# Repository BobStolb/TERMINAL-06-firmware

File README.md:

# TERMINAL-06 firmware

Six-digit Soviet nixie tube clock firmware — 4x IN-12A (HH:MM) + 2x IN-17 (SS),
built on Arduino Nano / ATmega328P.

Derived from [AlexGyver's NixieClock v2.5](https://github.com/AlexGyver/NixieClock_v2)
(MIT-spirited open project). Keep the original attribution if you redistribute
this source — see the header of `nixieClock_TS06.ino`.

## What's in here

- `firmware/nixieClock_TS06/` — the main clock sketch. Open
  `nixieClock_TS06.ino` in the Arduino IDE; the other `.ino` files in the same
  folder are tabs of the same sketch and compile together automatically.
  `nixieClock_TS06.hex` alongside them is a precompiled build — flashable
  directly with avrdude if you don't want to rebuild from source.
- `firmware/secCathodeMap/` — a standalone bench jig (its own `setup()`/
  `loop()`, deliberately kept in a separate sketch folder from the main
  firmware so the two don't collide at compile time). Run it once per new
  SEC module to map IN-17 cathodes to K155ID1 pins — see the comment header
  in `secCathodeMap.ino` for the full procedure.
- `libraries/` — actual source for the third-party libraries this sketch
  depends on: `GyverButton/` and `RTClib/`, each in the standard Arduino
  library layout (`.h`/`.cpp`, `library.properties`, examples). To build
  from scratch, copy both folders into your Arduino sketchbook's
  `libraries/` directory before compiling. Wire and EEPROM are built into
  the Arduino AVR core and don't need anything extra.

## Status vs. the project spec (as of 28.08.26)

This code is the display-layer port described in `TERMINAL-06-spec.md` §5:
six-tube multiplex ISR (Timer2 at AlexGyver's original prescaler 8, 50 Hz
refresh with 640 us of optocoupler dead time — see MULTIPLEX TIMING in the
sketch), anti-poisoning and glitch effects extended to all six tubes (both
now switchable off at build time, and currently off pending bench sign-off
of the timing), buzzer removed (D2 reused),
old rev B control scheme (2 buttons + 1 lever) — not the rotary/lever panel
described elsewhere in the project, which is a later firmware milestone.

**One known discrepancy, not yet fixed here:** the spec states `DOT_BRIGHT`
was retuned for neon (170/90) instead of the LED-era default (35/15), but
this source still has `DOT_BRIGHT 35` / `DOT_BRIGHT_N 15`
(`nixieClock_TS06.ino`). Doesn't affect the digit-multiplex testing this
firmware is used for (P2 in the prototype plan), but worth fixing before the
colon step (P6).

## Board settings for flashing

Arduino IDE: Board = Arduino Nano, Processor = ATmega328P. If upload fails
with a programmer-not-responding error, switch Processor to
"ATmega328P (Old Bootloader)" — common on CH340-based Nano clones.

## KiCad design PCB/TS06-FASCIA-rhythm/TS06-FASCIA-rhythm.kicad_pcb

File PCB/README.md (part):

# TERMINAL-06 — custom PCBs

The fascia goes to Rezonit with the clock's electronics. For a small production run, the electronics are the through-hole pair **TS06-DISP + TS06-DRV**: tubes on one board, everything else on the one behind it, no vias on either. The one-board TS06-MAIN is kept, with its history. A tube board of the old kind is deliberately deferred.

| Board | Size | Stack | Status |
|---|---|---|---|
| **TS06-FASCIA** | 176 × 40 mm | 2.0 mm FR4, black mask, white silk, ENIG | Routed. The control panel AND the printed product face. One board, not two. Surface-mount build: no solder visible from the front. Height compressed from the original 52mm 2026-09 - see below. |
| **TS06-FASCIA-rhythm** (fascia R) | 191.4 × 40 mm | 2.0 mm FR4, black mask, white silk, ENIG | **The fascia of the order** (`fab/ORDER.md`). Controls on the tubes' grid, surface-mount on the back, no plated hole. **Rev B (7.10.26): J1 is an upright JST B6B-PH-SM4-TB** (top entry: the plug stands off the back and the wires leave straight back; rev A had the side-entry S6B-PH-SM4-TB, whose lead bent 90 + 12 degrees onto the floor and cost the case 7.3 mm) - `PCB/TS06-FASCIA-rhythm/J1-UPRIGHT.md`, `PCB/TS06-FASCIA-rhythm/bom.md`. The 176 TS06-FASCIA above is unchanged (it keeps the side-entry part). |
| **TS06-FASCIA-THT** | 176 × 52 mm | same stack, ENIG | Second build of the same board, routed. Through-hole, with the A6 divider ON the face. Pick one to fabricate; they are alternatives, not a pair. Not yet height-compressed (the SMD build was chosen for fabrication). |
| **TS06-DISP** + **TS06-DRV** | 191.4 × 44 mm + 191.4 × 100 mm | 1.6 mm, matte black | **The through-hole pair (25.09.26), the build for a small production run.** A display board with the tubes and nothing else, plugged by pin strips into a driver board behind it, the way AlexGyver builds his. **Zero vias on either board.** Both at rev B (30.09.26): TS06-DRV rev B is routed and merged, `tools/verify_pair.sh` gives 27 PASS, 0 FAIL, 0 SKIP, and the fab packages are in `../fab/`. Not ordered. See below. |
| **TS06-MAIN** / **TS06-MAIN-THT** | 176 × 96 mm | 1.6 mm, matte black | **The whole clock on one board**, two builds, one outline, one netlist. Placed and checked; routing in progress — see below. Replaces the inherited AlexGyver board, SEC and COLON. |
| ~~TS06-SEC~~ | 67 × 55 mm | 1.6 mm, matte black | **Superseded 17.09.26 by TS06-MAIN.** Surface-mount build routed and clean (1159 tracks, 79 vias); kept as the worked example of a hard placement and of the router. |
| ~~TS06-COLON~~ | 6.5 mm strip | — | **Superseded 17.09.26 by TS06-MAIN**, which carries the two ИНС-1 at the same measured positions. Placement only. |
| ~~TS06-TUBE~~ | — | — | **Deferred 08.09.26.** See below. |

## The two builds of the fascia

Same outline, same artwork, same netlist, same connector. They differ in one decision:
where the solder is.

* **TS06-FASCIA** — every pad is surface-mount on the back face. The customer sees black
  mask, white silkscreen and the decorative gold, and no joint anywhere. Routed with 64
  signal tracks, all on B.Cu, and **zero vias anywhere on the board** — F.Cu carries only
  the decorative gold, so no signal net can ever collide with it. GND is a pour over the
  back face, same as THT, and reaches all 7 GND pads on its own: R6 (the A7 pull-up) used
  to sit directly in the corridor the other five nets needed to reach J1, walling three
  GND pads (SW4.1, R8.2, R7.2) off from the plane with no B.Cu path a router could find at
  any trace width. Moving R6 out of that corridor — no other placement changed — opened it
  up enough that the pour alone closes the gap, confirmed by checking every GND pad against
  KiCad's own computed `filled_polygon`, not just this repo's simulated one. No stitch
  traces, no vias, nothing extra: placement fixed what routing couldn't.
* **TS06-FASCIA-THT** — the A6 resistor ladder is on the FRONT: five axial resistors above
  the rotary's seven landing holes, and the copper between them is bare, so the divider
  reads as a circuit rather than as decoration. Every other part is behind the panel with
  its front mask closed, so those holes show no gold ring. Routed with 34 tracks and no
  vias: the ladder on F.Cu under opened mask, six signals on B.Cu under mask, and GND as a
  pour over the whole back face.

`preview.svg` (`preview.png` too, where regenerated) in each board's folder is generated
by `tools/render.py` from the board file itself — front face and back face — so the board
can be looked at without opening KiCad.

**TS06-FASCIA height compression (2026-09).** The board felt oversized next to the tube
row, so it was cut from 52mm to 40mm tall. This was a pure translation, not a re-route:
every footprint, all 64 tracks, the GND pour and the silkscreen legend were shifted up by
a fixed 12mm (the dead margin above the control row - SR25's 12.5mm lever-throw keepout
was the real floor, not the visible knob bezel), then the board outline itself was
redrawn 12mm shorter. Nothing about the routing was redesigned, so R6's placement (still
load-bearing for the GND pour closing without vias, see above) is untouched. The two
mounting holes nearest the top edge are the one exception: they're anchored to the board
edge, not the control row, so they were NOT shifted, keeping their original 4.5mm inset
from the (new) top edge. All five checker tools pass clean and match the pre-compression
board's output exactly (same 2 pour islands, same 86% coverage, same 12-net agreement
with the schematic). One thing the pure translation did NOT fix on its own: the MODE
dial's decorative arc (position labels 1-6, their tick marks, and the "MODE" title)
was drawn for the old 26mm-radius-from-center clearance and clipped the new 14mm
budget - the checker tools don't validate silkscreen against the board edge, only
copper, so this needed its own pass. Fixed by rescaling the whole arc/tick/number
system by 0.789 (position 1, the tallest point, now sits at 12.5mm above center
instead of 15.84mm) and moving the "MODE" title from directly above the shaft to
its left, clear of position 1's tick - it was the single tallest element (19mm)
and didn't belong to the numbered fan, so it got its own placement rather than
being scaled with the rest. `checkpcb.py`'s rotary-keepout check had the rotary's position
hardcoded as a literal (30.0, 26.0) from the old layout - fixed to read the rotary
footprint's real position instead, since a checker that only works for one specific
layout isn't a checker. TS06-FASCIA-THT was not touched - the SMD build was the one
chosen for fabrication.

**Two leftovers of that compression, fixed 30.09.26.**
* **Five circles moved by half.** The compression moved each circle's end point up 12 mm
  but not its centre. The rotary's 25 mm body ring, on F.SilkS, would have printed as a
  34.7 mm ring 12 mm below the knob and run 3.3 mm off the bottom edge. Its four siblings
  (lever and button keepouts on User.1) had the same fault. These were the board's only 2
  KiCad DRC warnings. All five centres are moved up 12 mm, so each radius is horizontal
  again (12.5 and 12.0 mm). The body ring is back on User.1, where `tools/mkpcb.py` drew it.
* **A stale ground fill.** The stored GND fill reached 11.5 mm above the top edge, and
  Gerbers plot the stored fill. KiCad 10 refilled the pour and saved the board.

After both fixes:
* KiCad DRC: 0 violations and 0 unconnected, at every severity.
* `checkpcb`, `checkcopper` and `audit`: clean.
* `checkmatch`: agrees with the schematic.

**One picture outlived the fix.** `PCB/TS06-FASCIA-rhythm/composite-0-centred.png`, the
reference that the fascia variants are judged against, was drawn from a board older than
the ring fix. So it still showed the ring 12 mm below the knob, and the owner's review
reported it as "the SW1 white circle isn't centred on its hole". It is redrawn from the
fixed board. `tools/mkpcb_fascia_rhythm.py` now refuses to draw a composite from a board
whose F.SilkS ring encloses a control hole off-centre (`silk_rings_off_centre()`).
`tools/render_kicad.py` renders a board in KiCad 10 with the black mask and white silk
that are ordered.

**Fascia R, rev B (7.10.26): J1 is upright.** The footprint `TS06_JST_PH_B6B-PH-SM4-TB_Back` (KiCad's land pattern, mirrored in X for the back; SMD, no plated hole) keeps the pin order and the place between the buttons; the case model's floor rose from Y -7.3 to -4.5 (204.4 × 120.0 × 81.0 mm outside). The rest of this section is about the 176 TS06-FASCIA.

**J1 pin order is fixed for both builds: 1 +5V, 2 GND, 3 A6, 4 A7, 5 D7, 6 D8.** It used
to be whatever the surface-mount routing preferred (D8, D7, GND, A7, +5V, A6). The
through-hole board cannot route to that order, and two builds of one product must not
need two different cables, so the pin order stopped being a layout convenience and became
a specification. The legend is printed on the back silkscreen of both boards.

## TS06-DISP + TS06-DRV — the through-hole pair (25.09.26)

**The clock as two stacked boards, the way AlexGyver builds his: a display board with the tubes
and nothing else, and a driver board behind it with everything else, joined by pin strips.**
Through-hole throughout, **no vias on either board**. The layout is designed as a whole, not
packed and then routed. This supersedes TS06-MAIN-THT as the build for a small production
run. TS06-MAIN (SMD) and its history stay as they are.

A critical review of the pair, and what it means for the case, is in
`../Claude outputs/TS06-pair-review.md`.

### Why two boards, and why these two

The one-board TS06-MAIN failed on the thing the owner cares most about:
* 476, then 339, then 177 vias;
* a ground pour in hundreds of islands;
* cathode switches squeezed into tube rings.

The split study (`../Claude outputs/TS06-split-study.md`) found an 18-wire cut. The owner chose
the Gyver cut instead: **tubes only on the display board**. The halves join the way Gyver joins
his, with a straight pin strip (PLS / рейка штыревая) on one board plugged into a socket strip
(PBS) on the other. No wires, no cable to make up.

That cut is what makes zero vias possible:
* The display board has no drivers, so its copper is only the tube wiring. The ИН-12 cathode
  bus can be threaded through the sockets on one face, as Gyver's tube half does it.
* The driver board has no tube fields, so every block can sit behind the strip pins it drives.

### Circuit changes for the pair (owner, 24.09.26)

| Change | Why |
|---|---|
| **ИН-15 pair on 2 × К155ИД1 + 1 × MCP23017** instead of 18 MPSA42 + 18 base resistors + 2 expanders | A symbol tube lights one glyph at a time, exactly like a digit, so a decoder does the whole job. 37 fewer parts, ~110 fewer joints. Firmware writes a code per tube; 10–15 blanks it. |
| **Every backlight LED addressable**: one MCP23017 port-B pin and one resistor per LED (RN1, an isolated 8 × 220 R network), cathodes common through the MPSA42 on D11 | A lit LED can show which tube's setting is being changed; D11 stays the global brightness PWM. |
| **A second К155ИД1 (U17) for the ИН-17 pair**, on the same A0–A3 lines | The display board delivers the ИН-12 bus and the ИН-17 bundle in the orders their tubes impose. One decoder feeding both would need a ten-line permutation, which two layers cannot make without vias. |
| **`BOARD_TYPE 4`** in the firmware | The pair's own digit map, `digitMask[] = {1, 0, 5, 4, 6, 7, 3, 2, 9, 8}`, and its own anode order `opts[]` (hours on D6/D5, minutes on D4/D3, S10 on D2, S1 on D13: the order types 1 and 2 use). The anode pins are the same six, driving different tubes, so the Nano's digital row fans out without crossing itself. |

Every other Nano pin keeps its function.

### The stack

**TS06-DISP**, 191.4 × 44 mm.
* **On its front:** 4 × ИН-12, 2 × ИН-17, 2 × ИН-15, 2 × ИНС-1 and 9 LEDs.
* **On its back, seven male strips:**
  * XP11 on the left edge (the ИН-12 bus);
  * XP12 on the top edge (31 pins: the ИН-17 bundle and both ИН-15, with 3 spares after pin 10);
  * XP21–XP25 on the bottom edge (anodes, colon, LEDs).
* **Silkscreen: the circuit as ornament** (the owner's choice of 30.09.26, from three art
  directions: "the best for display pcb is circuit as ornament"). It is drawn over rev B's labels
  by `tools/mkpcb_disp.py`, which writes it by default (`tools/disp_art.py`; `--art none` writes
  plain rev B). The art is the board's own circuit: the ИН-12 bus strands and the cathode order
  1 6 2 7 5 0 4 9 8 3 on the front, only where the finished clock shows the board, and every
  socket's pinout on the back. White silk only, lines from 0.15 mm, clear of every pad; the copper
  is unchanged. Three back-face pin labels are left out for room (H and m, the top pins of the two
  ИН-15; A, the ИН-15Б's ampere cathode); XP12's legend names all three.

**TS06-DRV**, 191.4 × 100 mm, sits 11 mm behind the display on M3 standoffs (a standard 8.5 mm
PBS socket plus a 2.5 mm PLS body). Its seven socket strips are on its **back** face, towards
the display. Every other part is on its front, towards the back of the case, so nothing taller
than the strips lives between the boards. It has three bands:
* **The top band, 26 mm above the display:**
  * the Nano across the top-right corner, its USB proud of the edge;
  * the 12 V jack through the other edge;
  * fuse, polarity diode and 5 V regulator;
  * the 185 V converter in one tight loop, with its driver and control block beside it, and
    (rev B) an over-voltage clamp that stops the switch at 225-270 V without the comparator.
* **The tube band, behind the display:**
  * the three К155ИД1 for the ИН-15 pair and the ИН-17 pair under the top strip;
  * U2 beside the left strip;
  * the six anode channels as three cells over the bottom strips: two resistors and two optos
    per pair of tubes. Rev B draws the resistors for МЛТ-0,5 (15.24 mm), so the seconds' cell lays
    its two back to back in one row and the minutes' and hours' cells keep two rows 5.0 mm apart.
* **The bottom band, 30 mm below the display:**
  * the MCP23017 with its LED network stacked on port B;
  * the RTC module;
  * J1, the fascia connector. It is top-entry, so the cable leaves straight towards the fascia.
    Rev B's 1 k + 10 nF on D7 and D8 and 1 M on A6 sit between the strips and J1, each part on its
    own line's way in, so the lines still fan into J1 in its pin order
    (`recovered/drv-revb/OPTIONS.md`: placed as a block in front of J1, they stalled the route).

The strip order is a specification shared by both boards (`tools/ts06pair.py HEADERS`).
`tools/mkpcb_drv.py` proves three things: every XS pin lands on its XP pin, it carries the
same net, and every display standoff has its hole.

**Why 191.4 mm, not 176** (29.09.26). The two ИН-17 were first drawn 13 mm apart, as every board
before had them, but their Ø20 stems need 20.5 (the tube's outline drawing; concept Rev F). The
owner chose to widen the boards and keep the Gyver pitch:
* the ИН-12s and the colon did not move;
* the seconds pair now stands 20.5 apart, each stem 2.2 mm from the glass beside it;
* the ИН-15 pair moved 15.4 mm right.

XP12 stays one strip of 31 pins, with three spares where the ИН-15 group moved further than the
ИН-17 group. On the driver board, what sits behind the ИН-17s moved 7.62 mm, and what sits behind
the ИН-12s, with the Nano and U2, moved 15.4. It was then re-routed. The review has the finding.

### How the driver board has no vias

A through-hole pad is copper on both faces, so it is the only place a net may change face.
The driver board is placed so that every crossing happens in a part the circuit already has.
There are no wire links and no zero-ohm jumpers.

The long buses are laid by hand, each on one face:
* **Port A of the expander:** out of the bottom of U3, up the left edge, and east under the
  two ИН-15 decoders, as one eight-line bus. In every bend, the inner line turns first.
* **The LED ribbon:** from the network up into lanes under the bottom strips. The two lines
  to the hours' strip run on the front face, so the back face under the strips is free for
  the button lines to cross on their way to J1.
* **The U17 branch of A0–A3:** it leaves under the Nano and runs down a corridor beside it.
  It enters U17 between the chip's rows, the one approach that lands every line on its own
  pin; from below, the bus would arrive mirrored.
* **D9, D10, D12 and D13:** they share that corridor and end in four standing resistors at
  its exit. Their outputs leave on the other face.

The Nano's fan-out below the module is also laid by hand:
* **The digital row, on the back face,** in lanes just below the module:
  * D2–D4 go to the minutes' and S10's opto resistors, standing under the module's end;
  * D5 and D6 go to the hours' opto resistors, lying straight above their optos;
  * D7, D8 and D11 go down the gap between the hours' cell and U2.
* **A7, A6, SCL and SDA, on the front face,** come down the same gap and west between the
  hours' optos' pin rows. They end in one column of their filters and pull-ups, in the order
  they arrive, and change face there.

Everything else is routed by `tools/netroute.py`, which never places a via. It uses negotiated
congestion (PathFinder), with diagonals priced above two straight steps, so long runs come out
square with 45° corners. A polish pass then re-routes each net alone. The result is saved in
`tools/mkpcb_drv_routes.json`, so the board regenerates exactly.

### Assembly-friendly by design

* **Every part is through-hole**, on standard footprints read out of KiCad 10's own libraries
  (`PCB/lib/TS06.pretty`). Nothing needs hot air or paste.
* **Every IC is in a socket and the Nano is on two PBS-15 strips**, so a dead chip or Nano is
  a swap, not a desolder.
* **References are on the silkscreen** of TS06-DRV's component face, and (rev B) the legends a
  builder needs: the block names, the 185 V areas fenced and marked "DANGER 185 V", "12 V DC,
  centre +" at the jack, "HV SET" at the trimmer, "fit U12 before U11", "USB only with 12 V on",
  the RTC module's "- NC C D +" and its outline, J1's pinout and every strip's pin 1 on the face
  towards the display, and the title. All at the fab's floor: 1.0 mm text, 0.15 mm lines, off
  every pad.
* **No wiring harness between the boards.** The fascia cable (JST PH, spec pin order) is the
  only cable.
* **The anode channels are drawn from one pattern**, so a mistake in one is easy to see in all.
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
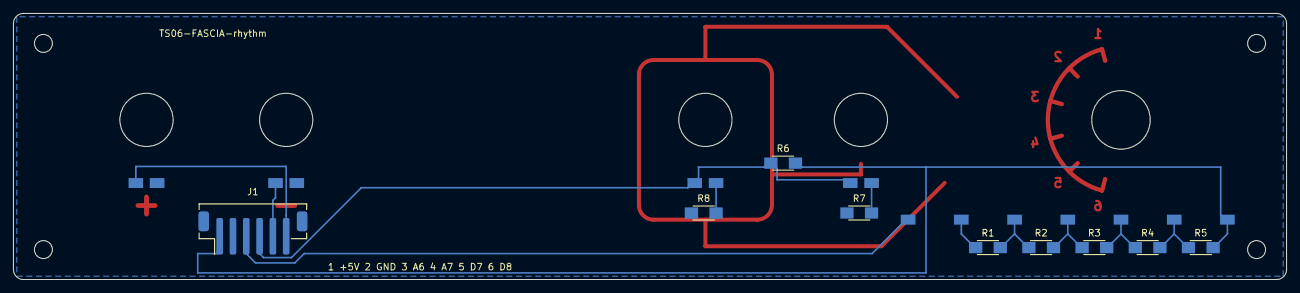
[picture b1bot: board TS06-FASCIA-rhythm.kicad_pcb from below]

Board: 2 copper layers, 191.4 x 40.0 mm, 18 parts (9 on the bottom side), 12 nets.

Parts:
H1, H2, H3, H4: MountingHole_2.7mm
J1: PH 6; TS06_JST_PH_B6B-PH-SM4-TB_Back
R1, R2, R3, R4, R5: 4k7; TS06_R_1206_HandSolder
R6, R8: 10k; TS06_R_1206_HandSolder
R7: 20k; TS06_R_1206_HandSolder
SW1: SR25 6-pos; TS06_Rotary_SR25_PanelMount_Rhythm
SW2: FIELD; TS06_MT1_Lever_PanelMount
SW3: SUB; TS06_MT1_Lever_PanelMount
SW4: MINUS; TS06_KMD1_Button_PanelMount
SW5: PLUS; TS06_KMD1_Button_PanelMount

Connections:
+5V: J1.1, R5.1, R6.1, SW1.6
A6: J1.3, SW1.7
A7: J1.4, R6.2, SW2.2, SW3.2
D7: J1.5, SW4.2
D8: J1.6, SW5.2
GND: J1.2, R1.2, R7.2, R8.2, SW1.1, SW4.1, SW5.1
LEVA: R7.1, SW2.1
LEVB: R8.1, SW3.1
TAP2: R1.1, R2.2, SW1.2
TAP3: R2.1, R3.2, SW1.3
TAP4: R3.1, R4.2, SW1.4
TAP5: R4.1, R5.2, SW1.5

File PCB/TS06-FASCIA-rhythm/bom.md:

# TS06-FASCIA-rhythm (fascia R) rev B: bill of materials

Hand-written from `tools/mkpcb_fascia_rhythm.py` (its `VALUE` and `FP` tables); there was no BOM for the fascia before. The pair's BOMs
(`PCB/TS06-DISP/bom.md`, `PCB/TS06-DRV/bom.md`) are generated by `tools/bom_pair.py`; this one is not. Board: 191.4 x 40 mm, 2.0 mm FR4,
black mask, white silk, ENIG (`fab/ORDER.md`). Every part is on the back, soldered by hand; no plated hole.

| Qty | Part | Refs | Footprint | Notes |
|---|---|---|---|---|
| 1 | **JST B6B-PH-SM4-TB**: PH 2.0 mm, 6 way, **top entry (upright)**, SMD, two retention tabs | J1 | `TS06_JST_PH_B6B-PH-SM4-TB_Back` | **Rev B (7 October 2026); rev A had the side-entry S6B-PH-SM4-TB.** The plug (PHR-6) stands straight off the back and the wires leave straight back. The tabs carry the load. Pin 1 = +5V at the right seen from the front. Header height 6.0 mm *inferred* (`PCB/TS06-FASCIA-rhythm/J1-UPRIGHT.md`) |
| 1 | SR25-style 6-position rotary (galette), panel mount, 12 detents of 30 degrees | SW1 | `TS06_Rotary_SR25_PanelMount_Rhythm` | MODE; bushing 8.62 mm in a 9.2 mm hole (opened 0.4 mm in the ordered zip); body 25.00 mm behind the panel |
| 2 | МТ1 toggle lever, panel mount | SW2, SW3 | `TS06_MT1_Lever_PanelMount` | FIELD, SUB; bushing 7.82 mm in an 8.4 mm hole (ordered zip) |
| 2 | КМД1-1 pushbutton, panel mount | SW4, SW5 | `TS06_KMD1_Button_PanelMount` | minus, plus; bushing 7.82 mm in an 8.4 mm hole (ordered zip) |
| 5 | 4k7, 1206 | R1-R5 | `TS06_R_1206_HandSolder` | the A6 ladder under the rotary's landing pads |
| 2 | 10k, 1206 | R6, R8 | `TS06_R_1206_HandSolder` | R6 the A7 pull-up; R8 the SUB lever's pull-down |
| 1 | 20k, 1206 | R7 | `TS06_R_1206_HandSolder` | the FIELD lever's pull-down |
| 4 | M2.5 screw, with the case's heat-set insert | H1-H4 | `MountingHole_2.7mm` | 2.7 mm holes at the corners; the screws are case hardware (`3d/case-pair`) |

The resistors' tolerance and power are not stated in the board file. The lead to TS06-DRV J1 (two PHR-6 housings and twelve SPH-002T-P0.5S
crimps, or a ready-made lead, 180-200 mm, pin 1 to pin 1) is on TS06-DRV's BOM; its fascia end plugs into the upright J1 above. The
controls are wired by hand from their lugs to the landing pads on the back (the product page's Wiring view shows them).

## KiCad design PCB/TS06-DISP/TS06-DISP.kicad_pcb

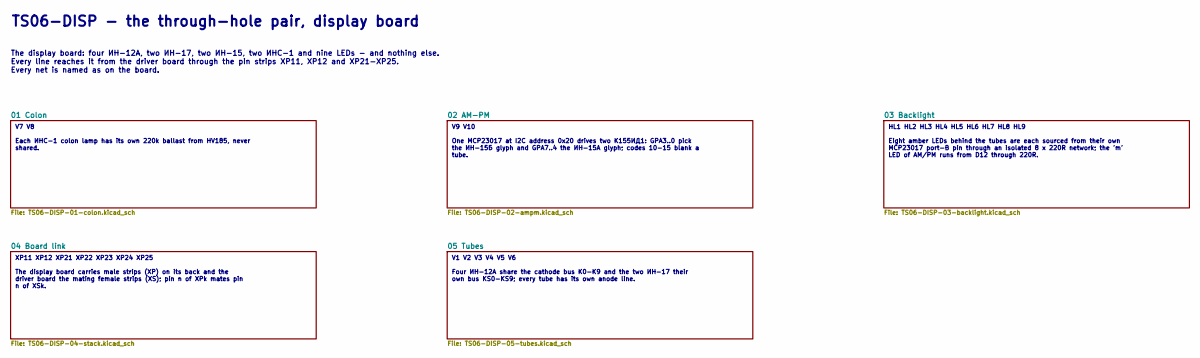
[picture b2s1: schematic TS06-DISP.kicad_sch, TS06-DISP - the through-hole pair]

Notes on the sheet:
TS06-DISP - the through-hole pair, display board
The display board: four ИН-12А, two ИН-17, two ИН-15, two ИНС-1 and nine LEDs - and nothing else. Every line reaches it from the driver board through the pin strips XP11, XP12 and XP21-XP25. Every net is named as on the board.
V7 V8 Each ИНС-1 colon lamp has its own 220k ballast from HV185, never shared.
V9 V10 One MCP23017 at I2C address 0x20 drives two К155ИД1: GPA3..0 pick the ИН-15Б glyph and GPA7..4 the ИН-15А glyph; codes 10-15 blank a tube.
HL1 HL2 HL3 HL4 HL5 HL6 HL7 HL8 HL9 Eight amber LEDs behind the tubes are each sourced from their own MCP23017 port-B pin through an isolated 8 x 220R network; the 'm' LED of AM/PM runs from D12 through 220R.
XP11 XP12 XP21 XP22 XP23 XP24 XP25 The display board carries male strips (XP) on its back and the driver board the mating female strips (XS); pin n of XPk mates pin n of XSk.
V1 V2 V3 V4 V5 V6 Four ИН-12А share the cathode bus K0-K9 and the two ИН-17 their own bus KS0-KS9; every tube has its own anode line.

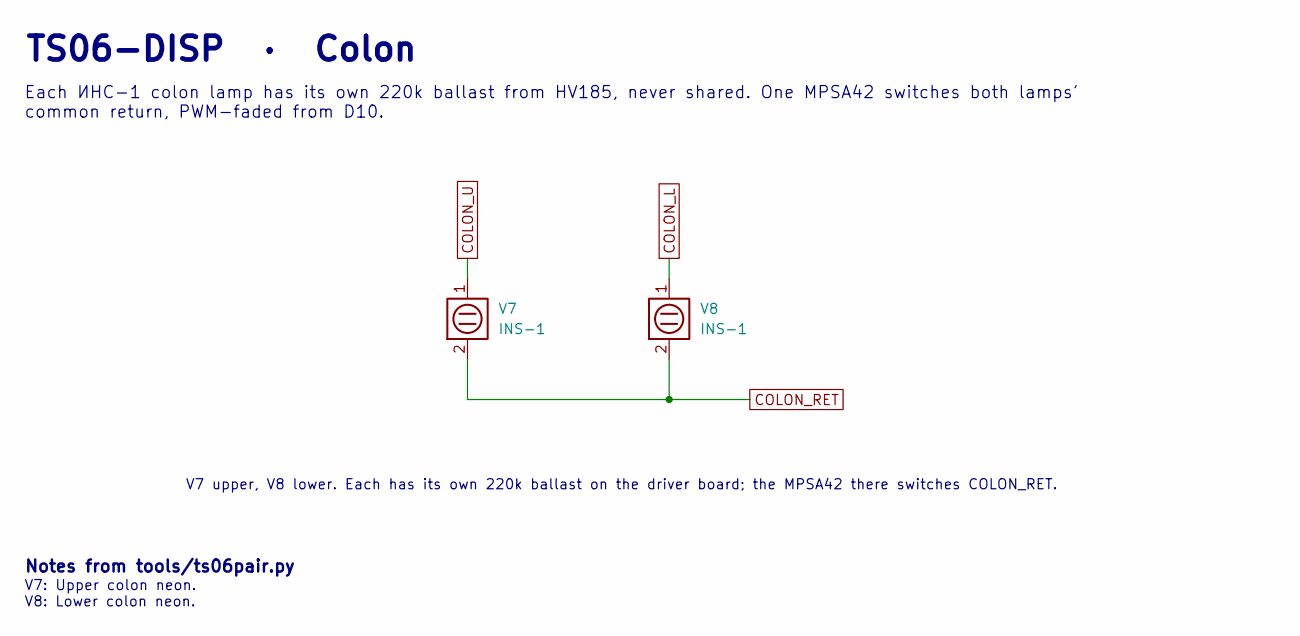
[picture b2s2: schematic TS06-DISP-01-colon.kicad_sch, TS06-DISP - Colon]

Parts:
V7, V8: INS-1; TS06_INS1_Lamp

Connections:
COLON_L: V8.1 (A); also elsewhere on the board
COLON_RET: V7.2 (K), V8.2 (K); also elsewhere on the board
COLON_U: V7.1 (A); also elsewhere on the board

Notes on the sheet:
TS06-DISP · Colon
Each ИНС-1 colon lamp has its own 220k ballast from HV185, never shared. One MPSA42 switches both lamps' common return, PWM-faded from D10.
V7 upper, V8 lower. Each has its own 220k ballast on the driver board; the MPSA42 there switches COLON_RET.
Notes from tools/ts06pair.py
V7: Upper colon neon. V8: Lower colon neon.

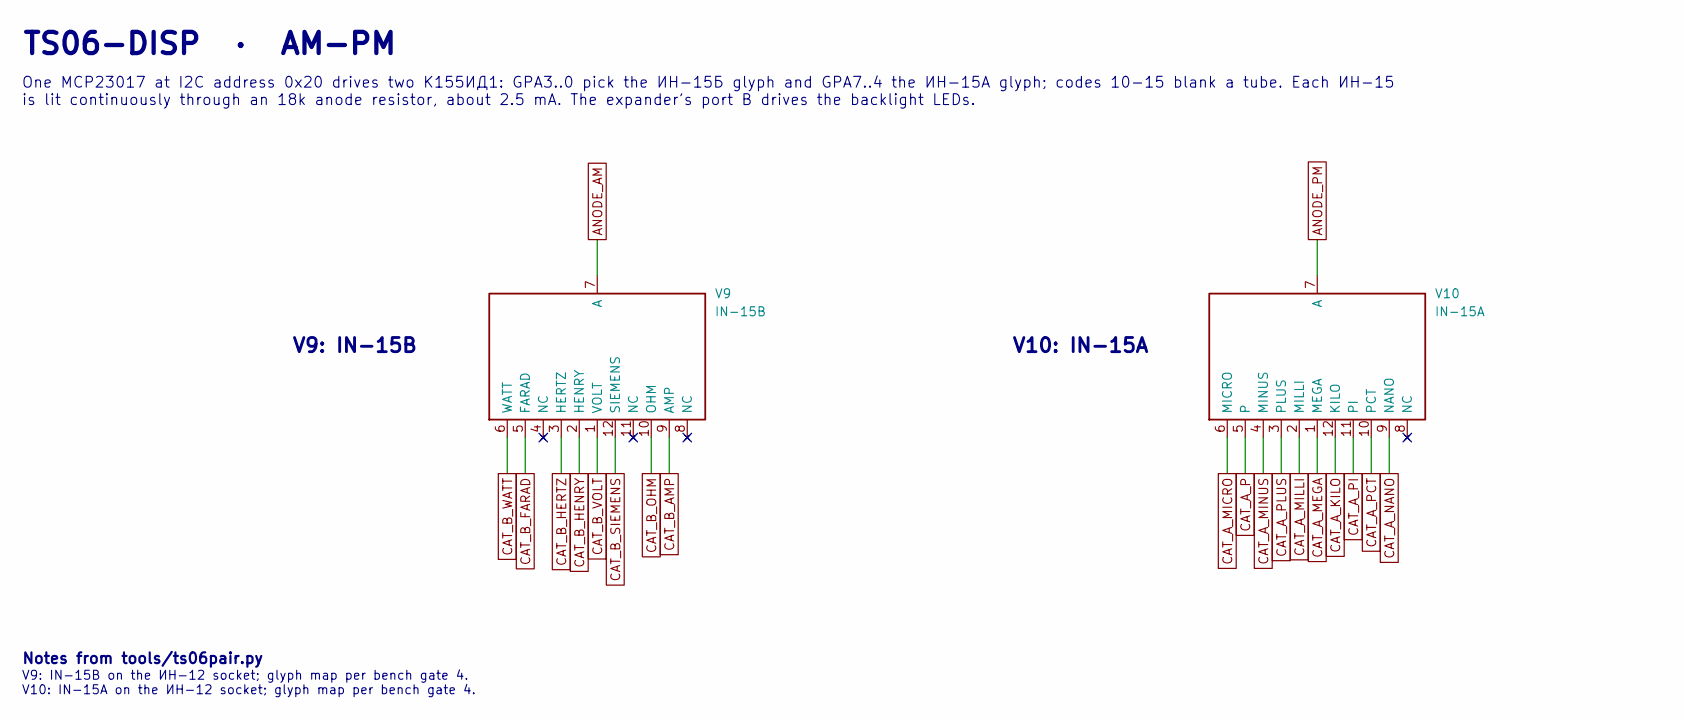
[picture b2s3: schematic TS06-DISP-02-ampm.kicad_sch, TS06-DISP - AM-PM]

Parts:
V9: IN-15B; TS06_IN12_Socket
V10: IN-15A; TS06_IN12_Socket

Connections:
ANODE_AM: V9.7 (A); also elsewhere on the board
ANODE_PM: V10.7 (A); also elsewhere on the board
CAT_A_KILO: V10.12 (KILO); also elsewhere on the board
CAT_A_MEGA: V10.1 (MEGA); also elsewhere on the board
CAT_A_MICRO: V10.6 (MICRO); also elsewhere on the board
CAT_A_MILLI: V10.2 (MILLI); also elsewhere on the board
CAT_A_MINUS: V10.4 (MINUS); also elsewhere on the board
CAT_A_NANO: V10.9 (NANO); also elsewhere on the board
CAT_A_P: V10.5; also elsewhere on the board
CAT_A_PCT: V10.10 (PCT); also elsewhere on the board
CAT_A_PI: V10.11 (PI); also elsewhere on the board
CAT_A_PLUS: V10.3 (PLUS); also elsewhere on the board
CAT_B_AMP: V9.9 (AMP); also elsewhere on the board
CAT_B_FARAD: V9.5 (FARAD); also elsewhere on the board
CAT_B_HENRY: V9.2 (HENRY); also elsewhere on the board
CAT_B_HERTZ: V9.3 (HERTZ); also elsewhere on the board
CAT_B_OHM: V9.10 (OHM); also elsewhere on the board
CAT_B_SIEMENS: V9.12 (SIEMENS); also elsewhere on the board
CAT_B_VOLT: V9.1 (VOLT); also elsewhere on the board
CAT_B_WATT: V9.6 (WATT); also elsewhere on the board

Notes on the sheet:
TS06-DISP · AM-PM
One MCP23017 at I2C address 0x20 drives two К155ИД1: GPA3..0 pick the ИН-15Б glyph and GPA7..4 the ИН-15А glyph; codes 10-15 blank a tube. Each ИН-15 is lit continuously through an 18k anode resistor, about 2.5 mA. The expander's port B drives the backlight LEDs.
V9: IN-15B
V10: IN-15A
Notes from tools/ts06pair.py
V9: IN-15B on the ИН-12 socket; glyph map per bench gate 4. V10: IN-15A on the ИН-12 socket; glyph map per bench gate 4.

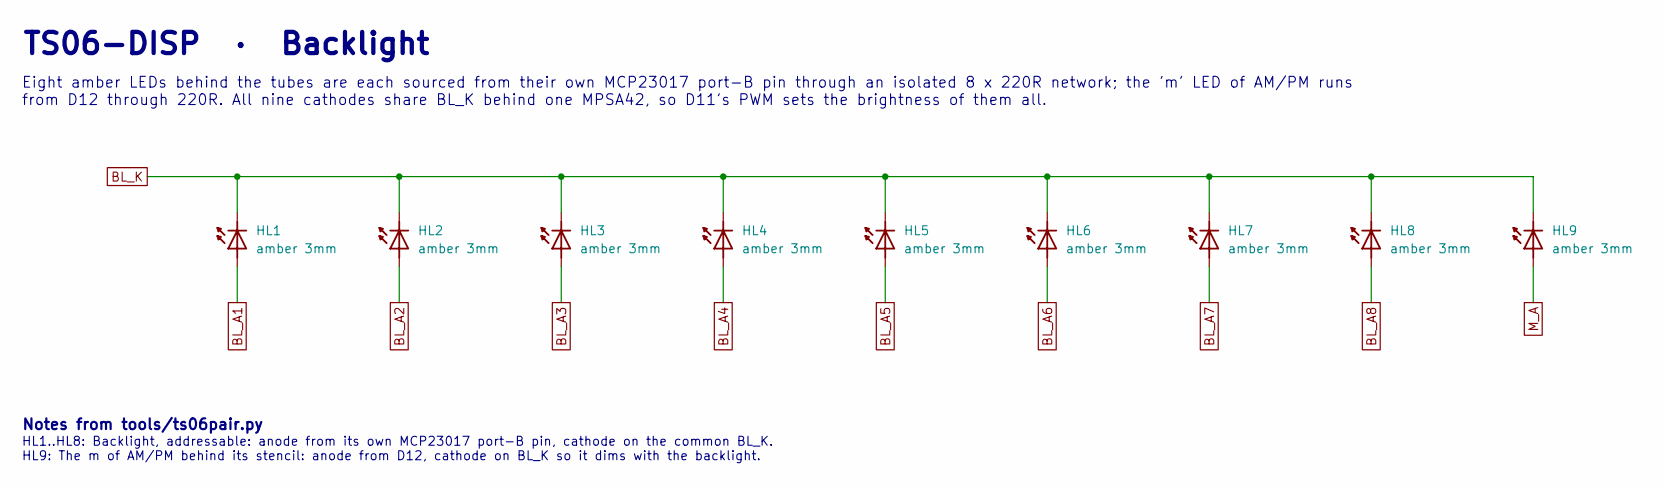
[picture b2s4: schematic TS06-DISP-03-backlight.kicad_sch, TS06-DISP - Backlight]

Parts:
HL1, HL2, HL3, HL4, HL5, HL6, HL7, HL8, HL9: amber 3mm; TS06_LED_D3.0mm

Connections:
BL_A1: HL1.2 (A); also elsewhere on the board
BL_A2: HL2.2 (A); also elsewhere on the board
BL_A3: HL3.2 (A); also elsewhere on the board
BL_A4: HL4.2 (A); also elsewhere on the board
BL_A5: HL5.2 (A); also elsewhere on the board
BL_A6: HL6.2 (A); also elsewhere on the board
BL_A7: HL7.2 (A); also elsewhere on the board
BL_A8: HL8.2 (A); also elsewhere on the board
BL_K: HL1.1 (K), HL2.1 (K), HL3.1 (K), HL4.1 (K), HL5.1 (K), HL6.1 (K), HL7.1 (K), HL8.1 (K), HL9.1 (K); also elsewhere on the board
M_A: HL9.2 (A); also elsewhere on the board

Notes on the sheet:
TS06-DISP · Backlight
Eight amber LEDs behind the tubes are each sourced from their own MCP23017 port-B pin through an isolated 8 x 220R network; the 'm' LED of AM/PM runs from D12 through 220R. All nine cathodes share BL_K behind one MPSA42, so D11's PWM sets the brightness of them all.
Notes from tools/ts06pair.py
HL1..HL8: Backlight, addressable: anode from its own MCP23017 port-B pin, cathode on the common BL_K. HL9: The m of AM/PM behind its stencil: anode from D12, cathode on BL_K so it dims with the backlight.

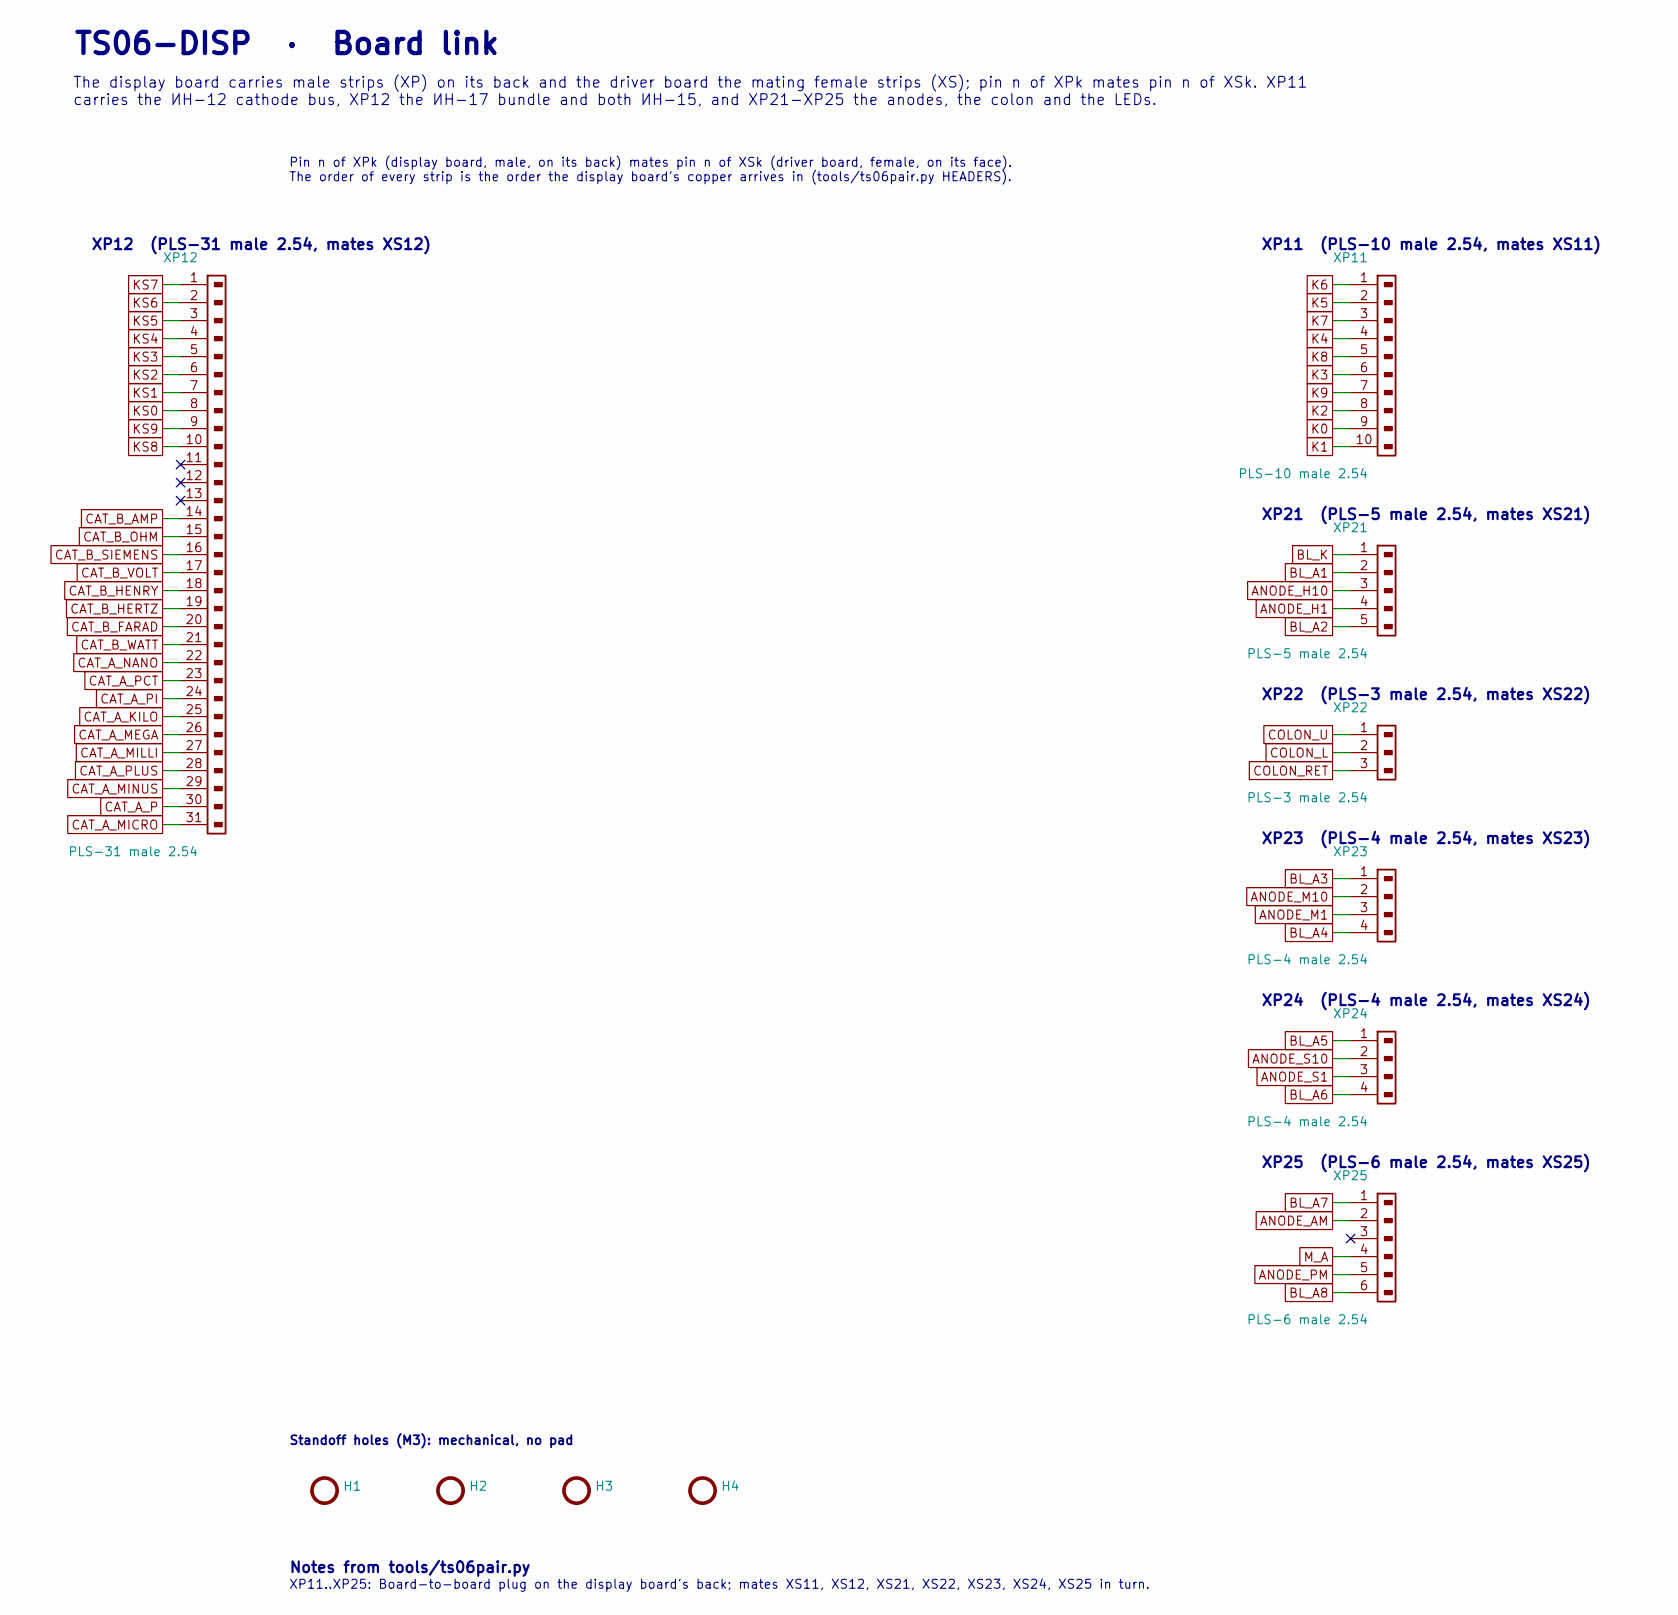
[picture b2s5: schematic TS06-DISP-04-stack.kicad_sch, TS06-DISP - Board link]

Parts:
H1, H2, H3, H4: TS06_MountingHole_M3
XP11: PLS-10 male 2.54; TS06_PinHeader_1x10_R180
XP12: PLS-31 male 2.54; TS06_PinHeader_1x31_R90
XP21: PLS-5 male 2.54; TS06_PinHeader_1x05_R90
XP22: PLS-3 male 2.54; TS06_PinHeader_1x03_R90
XP23, XP24: PLS-4 male 2.54; TS06_PinHeader_1x04_R90
XP25: PLS-6 male 2.54; TS06_PinHeader_1x06_R90

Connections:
ANODE_AM: XP25.2; also elsewhere on the board
ANODE_H1: XP21.4; also elsewhere on the board
ANODE_H10: XP21.3; also elsewhere on the board
ANODE_M1: XP23.3; also elsewhere on the board
ANODE_M10: XP23.2; also elsewhere on the board
ANODE_PM: XP25.5; also elsewhere on the board
ANODE_S1: XP24.3; also elsewhere on the board
ANODE_S10: XP24.2; also elsewhere on the board
BL_A1: XP21.2; also elsewhere on the board
BL_A2: XP21.5; also elsewhere on the board
BL_A3: XP23.1; also elsewhere on the board
BL_A4: XP23.4; also elsewhere on the board
BL_A5: XP24.1; also elsewhere on the board
BL_A6: XP24.4; also elsewhere on the board
BL_A7: XP25.1; also elsewhere on the board
BL_A8: XP25.6; also elsewhere on the board
BL_K: XP21.1; also elsewhere on the board
CAT_A_KILO: XP12.25; also elsewhere on the board
CAT_A_MEGA: XP12.26; also elsewhere on the board
CAT_A_MICRO: XP12.31; also elsewhere on the board
CAT_A_MILLI: XP12.27; also elsewhere on the board
CAT_A_MINUS: XP12.29; also elsewhere on the board
CAT_A_NANO: XP12.22; also elsewhere on the board
CAT_A_P: XP12.30; also elsewhere on the board
CAT_A_PCT: XP12.23; also elsewhere on the board
CAT_A_PI: XP12.24; also elsewhere on the board
CAT_A_PLUS: XP12.28; also elsewhere on the board
CAT_B_AMP: XP12.14; also elsewhere on the board
CAT_B_FARAD: XP12.20; also elsewhere on the board
CAT_B_HENRY: XP12.18; also elsewhere on the board
CAT_B_HERTZ: XP12.19; also elsewhere on the board
CAT_B_OHM: XP12.15; also elsewhere on the board
CAT_B_SIEMENS: XP12.16; also elsewhere on the board
CAT_B_VOLT: XP12.17; also elsewhere on the board
CAT_B_WATT: XP12.21; also elsewhere on the board
COLON_L: XP22.2; also elsewhere on the board
COLON_RET: XP22.3; also elsewhere on the board
COLON_U: XP22.1; also elsewhere on the board
K0: XP11.9; also elsewhere on the board
K1: XP11.10; also elsewhere on the board
K2: XP11.8; also elsewhere on the board
K3: XP11.6; also elsewhere on the board
K4: XP11.4; also elsewhere on the board
K5: XP11.2; also elsewhere on the board
K6: XP11.1; also elsewhere on the board
K7: XP11.3; also elsewhere on the board
K8: XP11.5; also elsewhere on the board
K9: XP11.7; also elsewhere on the board
KS0: XP12.8; also elsewhere on the board
KS1: XP12.7; also elsewhere on the board
KS2: XP12.6; also elsewhere on the board
KS3: XP12.5; also elsewhere on the board
KS4: XP12.4; also elsewhere on the board
KS5: XP12.3; also elsewhere on the board
KS6: XP12.2; also elsewhere on the board
KS7: XP12.1; also elsewhere on the board
KS8: XP12.10; also elsewhere on the board
KS9: XP12.9; also elsewhere on the board
M_A: XP25.4; also elsewhere on the board

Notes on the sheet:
TS06-DISP · Board link
The display board carries male strips (XP) on its back and the driver board the mating female strips (XS); pin n of XPk mates pin n of XSk. XP11 carries the ИН-12 cathode bus, XP12 the ИН-17 bundle and both ИН-15, and XP21-XP25 the anodes, the colon and the LEDs.
XP12 (PLS-31 male 2.54, mates XS12)
XP11 (PLS-10 male 2.54, mates XS11)
XP21 (PLS-5 male 2.54, mates XS21)
XP22 (PLS-3 male 2.54, mates XS22)
XP23 (PLS-4 male 2.54, mates XS23)
XP24 (PLS-4 male 2.54, mates XS24)
XP25 (PLS-6 male 2.54, mates XS25)
Pin n of XPk (display board, male, on its back) mates pin n of XSk (driver board, female, on its face). The order of every strip is the order the display board's copper arrives in (tools/ts06pair.py HEADERS).
Standoff holes (M3): mechanical, no pad
Notes from tools/ts06pair.py
XP11..XP25: Board-to-board plug on the display board's back; mates XS11, XS12, XS21, XS22, XS23, XS24, XS25 in turn.

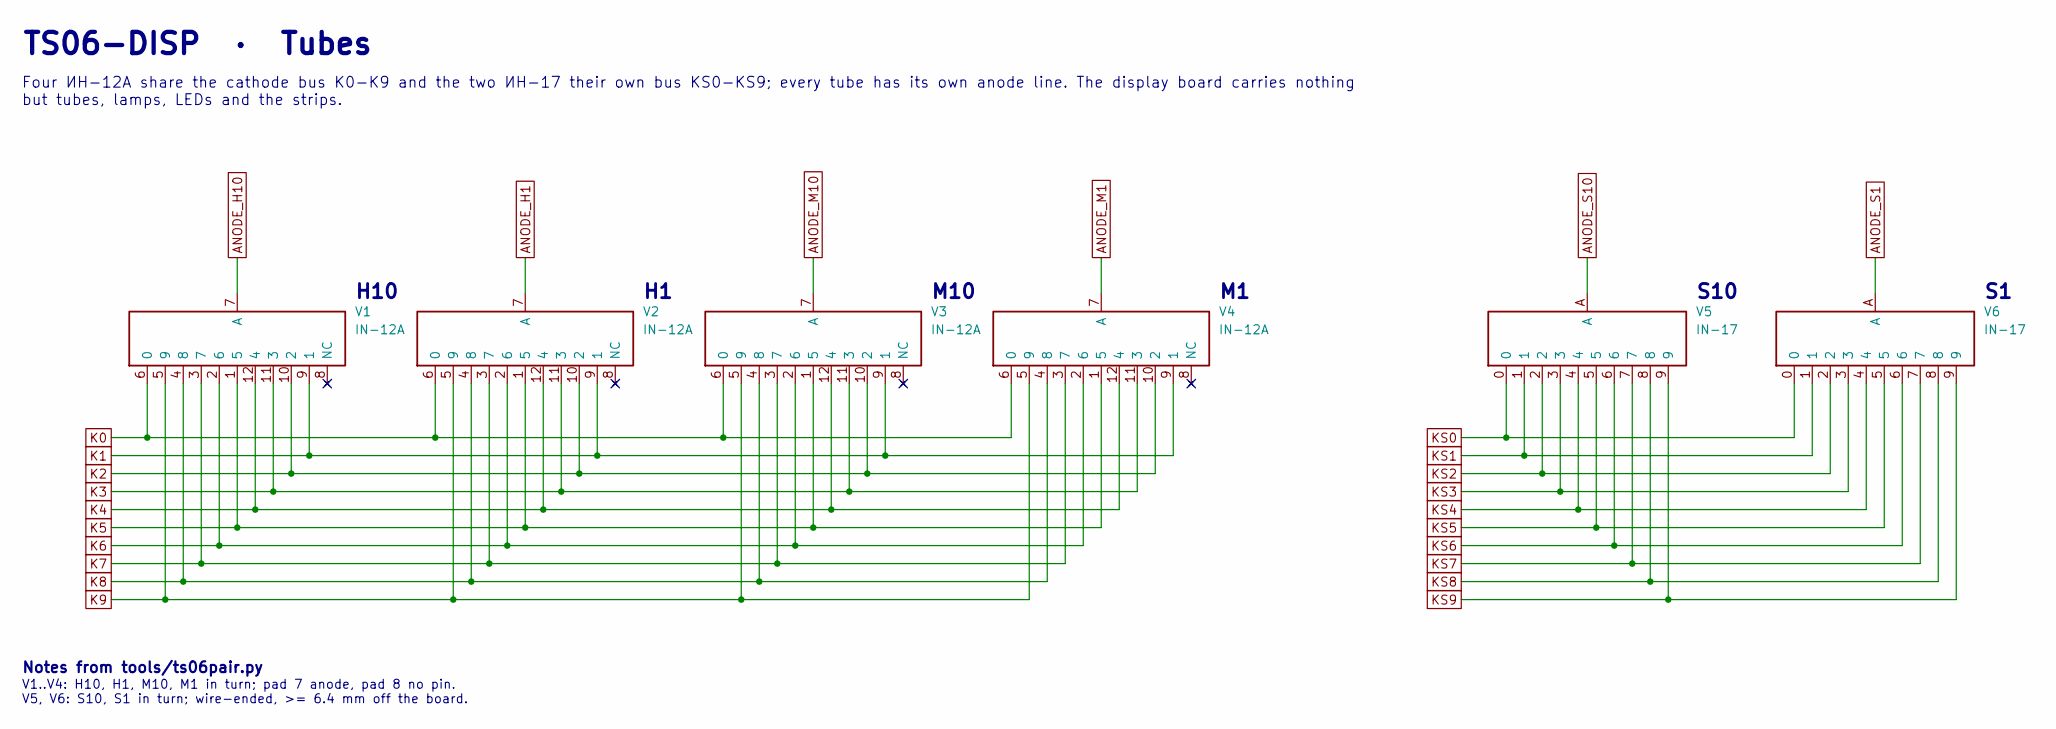
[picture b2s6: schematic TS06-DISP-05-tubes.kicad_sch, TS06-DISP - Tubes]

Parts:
V1, V2, V3, V4: IN-12A; TS06_IN12_Socket
V5, V6: IN-17; TS06_IN17_Socket

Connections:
ANODE_H1: V2.7 (A); also elsewhere on the board
ANODE_H10: V1.7 (A); also elsewhere on the board
ANODE_M1: V4.7 (A); also elsewhere on the board
ANODE_M10: V3.7 (A); also elsewhere on the board
ANODE_S1: V6.A; also elsewhere on the board
ANODE_S10: V5.A; also elsewhere on the board
K0: V1.6 (0), V2.6 (0), V3.6 (0), V4.6 (0); also elsewhere on the board
K1: V1.9 (1), V2.9 (1), V3.9 (1), V4.9 (1); also elsewhere on the board
K2: V1.10 (2), V2.10 (2), V3.10 (2), V4.10 (2); also elsewhere on the board
K3: V1.11 (3), V2.11 (3), V3.11 (3), V4.11 (3); also elsewhere on the board
K4: V1.12 (4), V2.12 (4), V3.12 (4), V4.12 (4); also elsewhere on the board
K5: V1.1 (5), V2.1 (5), V3.1 (5), V4.1 (5); also elsewhere on the board
K6: V1.2 (6), V2.2 (6), V3.2 (6), V4.2 (6); also elsewhere on the board
K7: V1.3 (7), V2.3 (7), V3.3 (7), V4.3 (7); also elsewhere on the board
K8: V1.4 (8), V2.4 (8), V3.4 (8), V4.4 (8); also elsewhere on the board
K9: V1.5 (9), V2.5 (9), V3.5 (9), V4.5 (9); also elsewhere on the board
KS0: V5.0, V6.0; also elsewhere on the board
KS1: V5.1, V6.1; also elsewhere on the board
KS2: V5.2, V6.2; also elsewhere on the board
KS3: V5.3, V6.3; also elsewhere on the board
KS4: V5.4, V6.4; also elsewhere on the board
KS5: V5.5, V6.5; also elsewhere on the board
KS6: V5.6, V6.6; also elsewhere on the board
KS7: V5.7, V6.7; also elsewhere on the board
KS8: V5.8, V6.8; also elsewhere on the board
KS9: V5.9, V6.9; also elsewhere on the board

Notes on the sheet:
TS06-DISP · Tubes
Four ИН-12А share the cathode bus K0-K9 and the two ИН-17 their own bus KS0-KS9; every tube has its own anode line. The display board carries nothing but tubes, lamps, LEDs and the strips.
H10
M10
S10
Notes from tools/ts06pair.py
V1..V4: H10, H1, M10, M1 in turn; pad 7 anode, pad 8 no pin. V5, V6: S10, S1 in turn; wire-ended, >= 6.4 mm off the board.

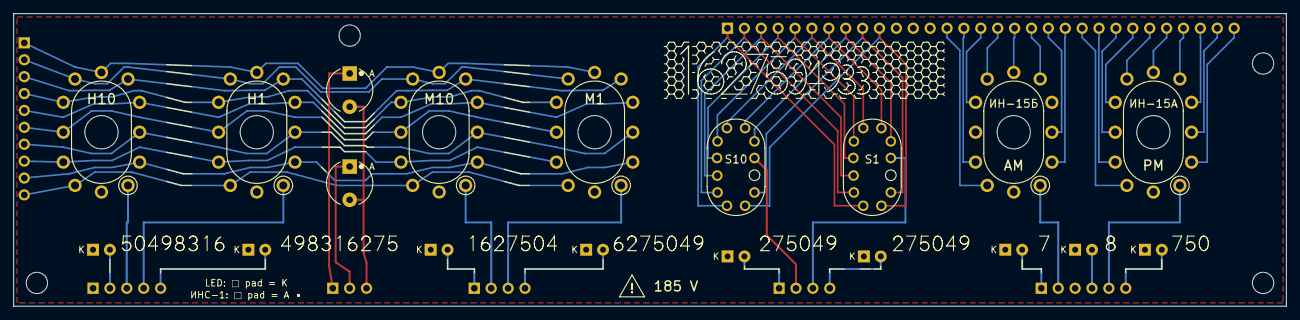
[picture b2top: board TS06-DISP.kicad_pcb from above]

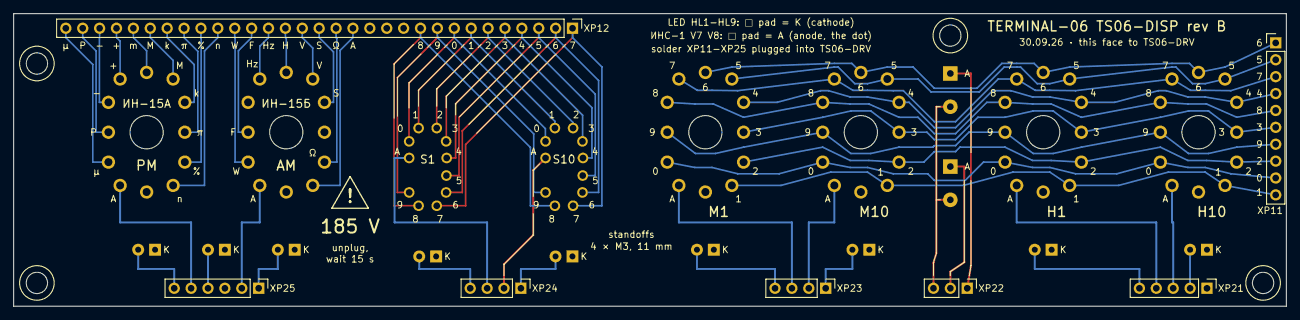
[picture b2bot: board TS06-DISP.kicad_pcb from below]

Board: 2 copper layers, 191.4 x 44.0 mm, 30 parts (7 on the bottom side), 59 nets.

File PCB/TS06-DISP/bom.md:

# TS06-DISP — bill of materials

Generated by `tools/bom_pair.py` from `tools/ts06pair.py`; do not edit by hand.
26 parts fitted, 0 footprints left empty. Every part is through-hole.

| Qty | Part | Value | Footprint | References |
|---|---|---|---|---|
| 9 | LED, 3 mm | amber 3mm | TS06_LED_D3.0mm | HL1, HL2, HL3, HL4, HL5, HL6, HL7, HL8, HL9 |
| 2 | Neon lamp | INS-1 | TS06_INS1_Lamp | V7, V8 |
| 4 | Nixie tube | IN-12A | TS06_IN12_Socket | V1, V2, V3, V4 |
| 1 | Nixie tube | IN-15A | TS06_IN12_Socket | V10 |
| 1 | Nixie tube | IN-15B | TS06_IN12_Socket | V9 |
| 2 | Nixie tube | IN-17 | TS06_IN17_Socket | V5, V6 |
| 1 | Pin header, straight (PLS) | PLS-10 male 2.54 | TS06_PinHeader_1x10 | XP11 |
| 1 | Pin header, straight (PLS) | PLS-3 male 2.54 | TS06_PinHeader_1x03 | XP22 |
| 1 | Pin header, straight (PLS) | PLS-31 male 2.54 | TS06_PinHeader_1x31 | XP12 |
| 2 | Pin header, straight (PLS) | PLS-4 male 2.54 | TS06_PinHeader_1x04 | XP23, XP24 |
| 1 | Pin header, straight (PLS) | PLS-5 male 2.54 | TS06_PinHeader_1x05 | XP21 |
| 1 | Pin header, straight (PLS) | PLS-6 male 2.54 | TS06_PinHeader_1x06 | XP25 |

## Hardware

| Qty | Item | For |
|---|---|---|
| 4 | Standoff M3, 11 mm, female-female, **nylon** (or brass with nylon washers at both ends), with 8 M3 × 6 screws | the four holes shared with TS06-DRV (11 mm = 8.5 mm PBS + 2.5 mm PLS body). Tracks pass 2.2-2.4 mm from H3's centre on both boards, under a metal standoff's 2.75-3.2 |
| 72 | Tube socket contact, 12 per tube; its tail must suit the 1.2 mm finished hole (choose the part, then check) | V1–V4 (ИН-12), V9–V10 (ИН-15) |
| 2 | ИН-17 spacer, holds the glass ≥ 6.4 mm off the board (the ТУ's 8 mm soldering rule) | V5, V6 |

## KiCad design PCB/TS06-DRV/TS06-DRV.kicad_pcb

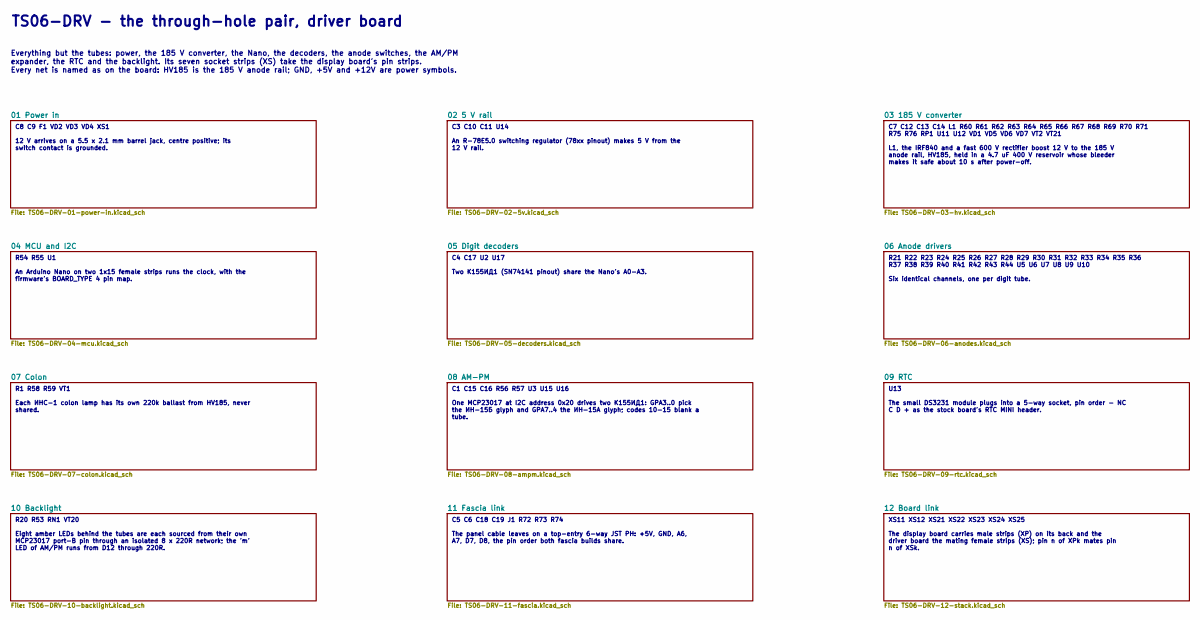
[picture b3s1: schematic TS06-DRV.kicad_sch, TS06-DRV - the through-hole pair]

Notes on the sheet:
TS06-DRV - the through-hole pair, driver board
Everything but the tubes: power, the 185 V converter, the Nano, the decoders, the anode switches, the AM/PM expander, the RTC and the backlight. Its seven socket strips (XS) take the display board's pin strips. Every net is named as on the board: HV185 is the 185 V anode rail; GND, +5V and +12V are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
C8 C9 F1 VD2 VD3 VD4 XS1 12 V arrives on a 5.5 x 2.1 mm barrel jack, centre positive; its switch contact is grounded.
C3 C10 C11 U14 An R-78E5.0 switching regulator (78xx pinout) makes 5 V from the 12 V rail.
C7 C12 C13 C14 L1 R60 R61 R62 R63 R64 R65 R66 R67 R68 R69 R70 R71 R75 R76 RP1 U11 U12 VD1 VD5 VD6 VD7 VT2 VT21 L1, the IRF840 and a fast 600 V rectifier boost 12 V to the 185 V anode rail, HV185, held in a 4.7 uF 400 V reservoir whose bleeder makes it safe about 10 s after power-off.
R54 R55 U1 An Arduino Nano on two 1x15 female strips runs the clock, with the firmware's BOARD_TYPE 4 pin map.
C4 C17 U2 U17 Two К155ИД1 (SN74141 pinout) share the Nano's A0-A3.
R21 R22 R23 R24 R25 R26 R27 R28 R29 R30 R31 R32 R33 R34 R35 R36 R37 R38 R39 R40 R41 R42 R43 R44 U5 U6 U7 U8 U9 U10 Six identical channels, one per digit tube.
R1 R58 R59 VT1 Each ИНС-1 colon lamp has its own 220k ballast from HV185, never shared.
C1 C15 C16 R56 R57 U3 U15 U16 One MCP23017 at I2C address 0x20 drives two К155ИД1: GPA3..0 pick the ИН-15Б glyph and GPA7..4 the ИН-15А glyph; codes 10-15 blank a tube.
U13 The small DS3231 module plugs into a 5-way socket, pin order - NC C D + as the stock board's RTC MINI header.
R20 R53 RN1 VT20 Eight amber LEDs behind the tubes are each sourced from their own MCP23017 port-B pin through an isolated 8 x 220R network; the 'm' LED of AM/PM runs from D12 through 220R.
C5 C6 C18 C19 J1 R72 R73 R74 The panel cable leaves on a top-entry 6-way JST PH: +5V, GND, A6, A7, D7, D8, the pin order both fascia builds share.
XS11 XS12 XS21 XS22 XS23 XS24 XS25 The display board carries male strips (XP) on its back and the driver board the mating female strips (XS); pin n of XPk mates pin n of XSk.
